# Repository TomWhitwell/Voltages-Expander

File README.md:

# Voltages Expander for the Turing Machine 

Hardware documentation for the old Voltages Fader Expander for the Music Thing Modular Turing Machine, published CC-BY-SA. 

For more details, visit http://www.musicthing.co.uk/

Qty | Value | Device | Parts | Description | Mouser
-- | -- | -- | -- | -- | --
8 | 50k | Illuminated Fader | GATE1, GATE2, GATE3, GATE4, GATE5, GATE6, GATE7, GATE8 | 20mm Alpha Illuminated Fader | 312-2045F-R50K
1 | 10k | 9mm pot | SCALE | 9 mm vertical pot, D shaft | 688-RK09K1130AH1
1 | 50k | 9mm pot | OFFSET | 9 mm vertical pot, D shaft | 652-PTV09A-4025FB503
2 | 100n | C-EU025-024X044 | C1, C2 | CAPACITOR | 594-K104K15X7RF5TH5
1 | TL074 | TL074 | IC1 | OP AMP | 595-TL074CN
1 |   | MA08-2 | GATES | PIN HEADER 2x8 | 649-67997-216HLF
1 | 78L09 |   | 78L1 | Positive VOLTAGE REGULATOR | 511-L78L09ACZ
6 | 10k | R-EU_0207/10 | R3, R4, R5, R6, R7, R8 | RESISTOR | 660-MF1/4DCT52A1002F
4 | 1k | R-EU_0207/10 | R1, R2, R9, R10 | RESISTOR | 660-MF1/4DCT52R1001F
1 | 10k | RN08 | RN1 | Resistor Network 9 pin, 8 resistors, bussed | 652-4609X-1LF-10K
1 | 2k | RN08 | RN2 | Resistor Network 9 pin, 8 resistors, bussed | 652-4609X-1LF-2K
3 | PJ-301B | PJ-301B | CLOCK_OUT, INVERT_OUT, MAIN_OUT | Sockets | Available from Erthenvar or Thonk
1 |   |   | 14 pin DIP socket |   | 649-DILB14P-223TLF
  |   |   |   |   |

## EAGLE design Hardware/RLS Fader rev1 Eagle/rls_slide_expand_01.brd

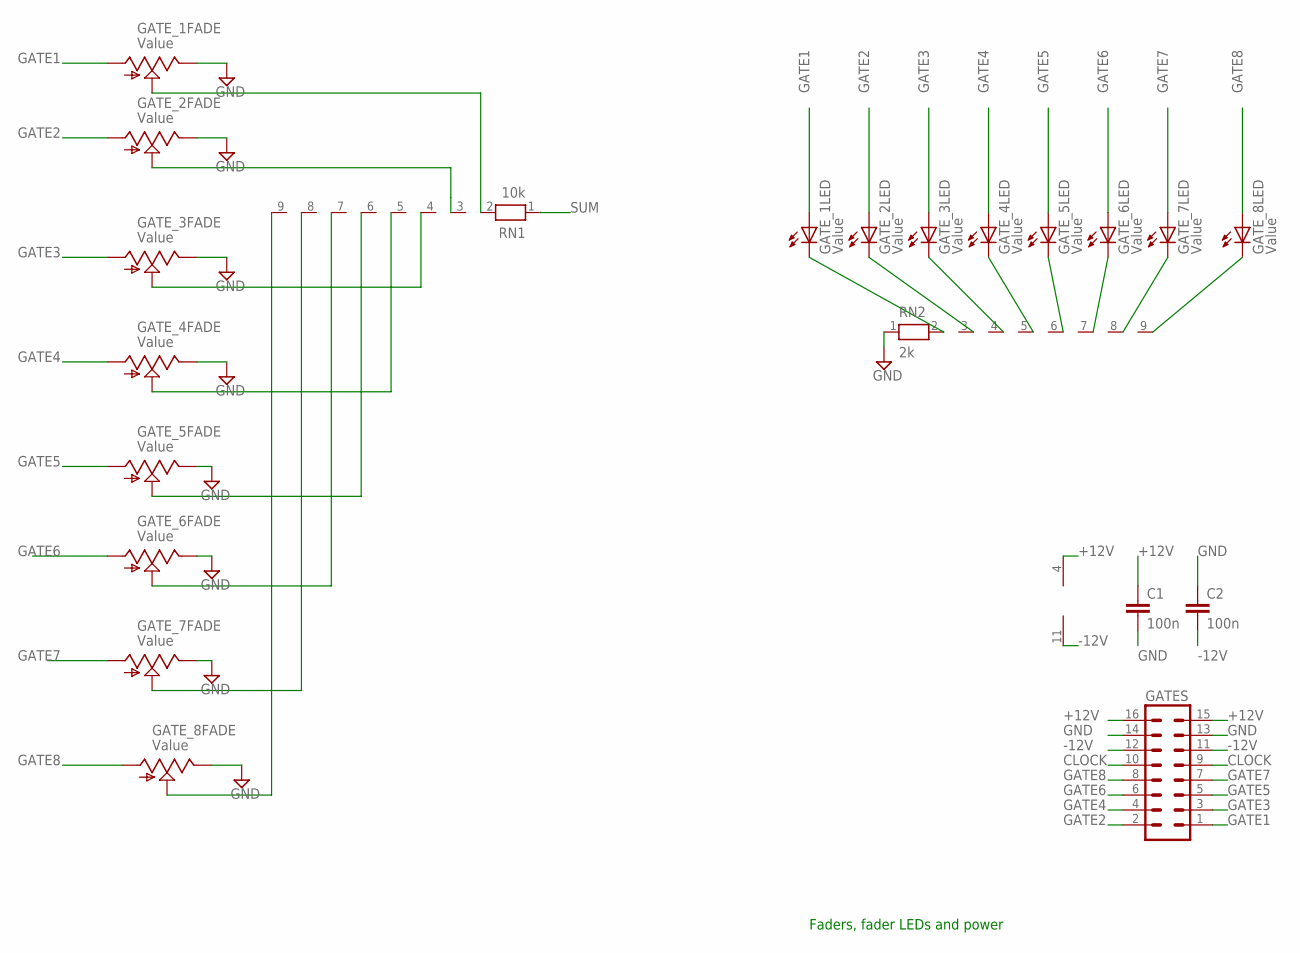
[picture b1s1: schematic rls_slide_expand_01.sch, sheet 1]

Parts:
C1, C2: 100n; C050-024X044
GATES: MA08-2
GATE_1, GATE_2, GATE_3, GATE_4, GATE_5, GATE_6, GATE_7, GATE_8: Value; ALPHA_ILL_FADER_20MM
IC1: TL074P; DIL14
RN1: 10k; RN-9
RN2: 2k; RN-9

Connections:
+12V: C1.1, GATES.15, GATES.16, IC1.4 (V+); also elsewhere on the board
-12V: C2.2, GATES.11, GATES.12, IC1.11 (V-)
CLOCK: GATES.9, GATES.10; also elsewhere on the board
GATE1: GATES.1, GATE_1.3 (A), GATE_1.B (A)
GATE2: GATES.2, GATE_2.3 (A), GATE_2.B (A)
GATE3: GATES.3, GATE_3.3 (A), GATE_3.B (A)
GATE4: GATES.4, GATE_4.3 (A), GATE_4.B (A)
GATE5: GATES.5, GATE_5.3 (A), GATE_5.B (A)
GATE6: GATES.6, GATE_6.3 (A), GATE_6.B (A)
GATE7: GATES.7, GATE_7.3 (A), GATE_7.B (A)
GATE8: GATES.8, GATE_8.3 (A), GATE_8.B (A)
GND: C1.2, C2.1, GATES.13, GATES.14, GATE_1.1 (E), GATE_2.1 (E), GATE_3.1 (E), GATE_4.1 (E), GATE_5.1 (E), GATE_6.1 (E), GATE_7.1 (E), GATE_8.1 (E), RN2.1; also elsewhere on the board
unnamed: GATE_1.2 (S), RN1.2
unnamed: GATE_1.E (C), RN2.2
unnamed: GATE_2.2 (S), RN1.3
unnamed: GATE_2.E (C), RN2.3
unnamed: GATE_3.E (C), RN2.4
unnamed: GATE_3.2 (S), RN1.4
unnamed: GATE_4.2 (S), RN1.5
unnamed: GATE_5.2 (S), RN1.6
unnamed: GATE_6.2 (S), RN1.7
unnamed: GATE_7.2 (S), RN1.8
unnamed: GATE_8.2 (S), RN1.9
unnamed: GATE_4.E (C), RN2.5
unnamed: GATE_6.E (C), RN2.7
unnamed: GATE_5.E (C), RN2.6
unnamed: GATE_7.E (C), RN2.8
unnamed: GATE_8.E (C), RN2.9
SUM: RN1.1; also elsewhere on the board

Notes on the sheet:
Faders, fader LEDs and power

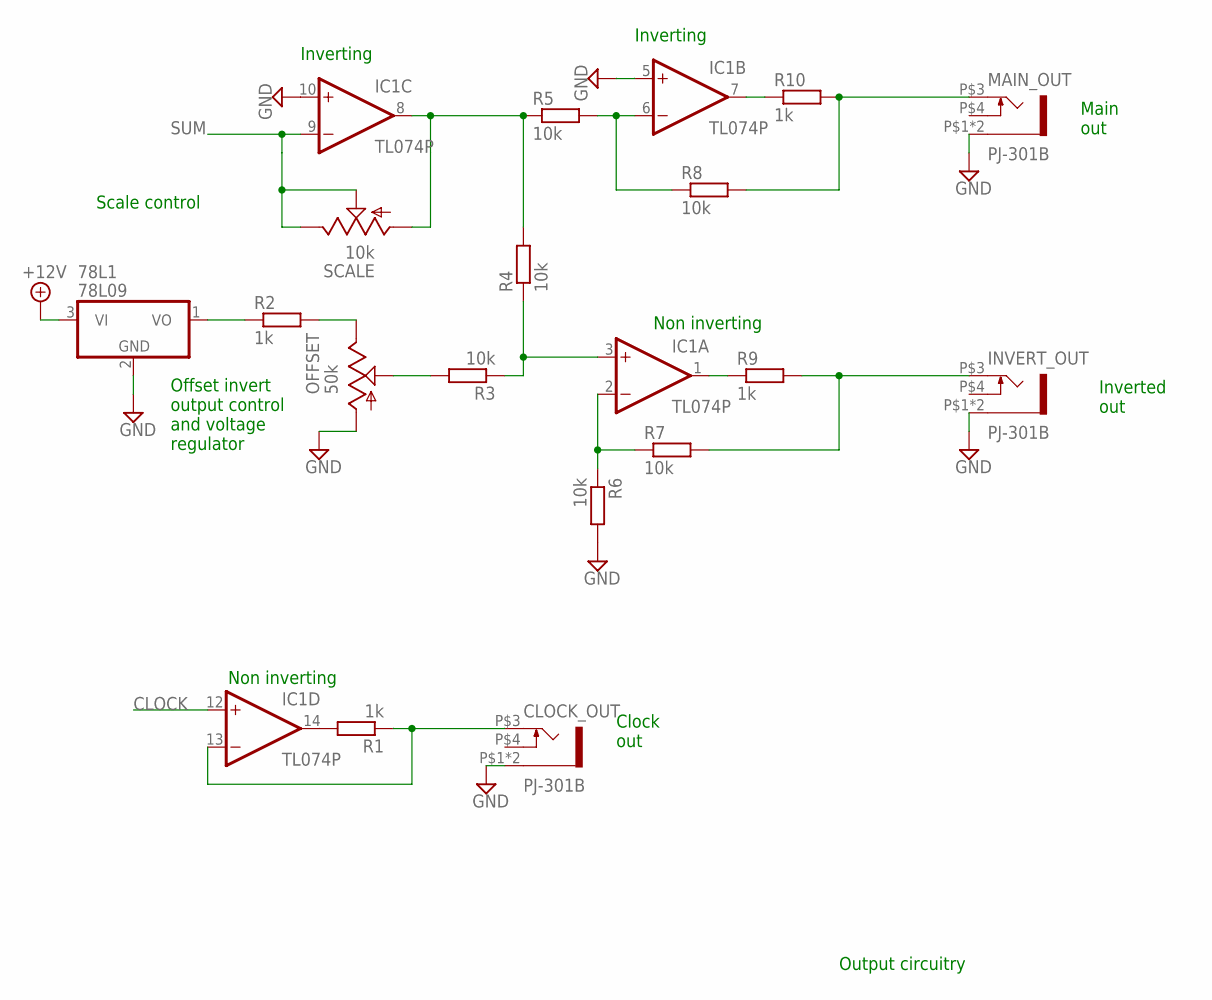
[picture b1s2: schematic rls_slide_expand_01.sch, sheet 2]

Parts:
78L1: 78L09; TO92
CLOCK_OUT: PJ-301B
IC1: TL074P; DIL14
INVERT_OUT: PJ-301B
MAIN_OUT: PJ-301B
OFFSET: 50k; EVUF
R1, R2, R9, R10: 1k; 0207/10
R3, R4, R5, R6, R7, R8: 10k; 0207/10
SCALE: 10k; EVUF

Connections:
+12V: 78L1.3 (VI); also elsewhere on the board
CLOCK: IC1.12 (+IN); also elsewhere on the board
GND: 78L1.2 (GND), CLOCK_OUT.P$1 (5), CLOCK_OUT.P$2 (5), IC1.5 (+IN), IC1.10 (+IN), INVERT_OUT.P$1 (5), INVERT_OUT.P$2 (5), MAIN_OUT.P$1 (5), MAIN_OUT.P$2 (5), OFFSET.1 (A), R6.2; also elsewhere on the board
unnamed: IC1.6 (-IN), R5.2, R8.1
unnamed: MAIN_OUT.P$3 (3), R8.2, R10.2
unnamed: IC1.7 (OUT), R10.1
unnamed: OFFSET.3 (E), R2.2
unnamed: IC1.1 (OUT), R9.1
unnamed: OFFSET.2 (S), R3.2
unnamed: IC1.3 (+IN), R3.1, R4.1
unnamed: IC1.2 (-IN), R6.1, R7.1
unnamed: INVERT_OUT.P$3 (3), R7.2, R9.2
unnamed: IC1.8 (OUT), R4.2, R5.1, SCALE.1 (A)
unnamed: IC1.14 (OUT), R1.2
unnamed: CLOCK_OUT.P$3 (3), IC1.13 (-IN), R1.1
unnamed: 78L1.1 (VO), R2.1
SUM: IC1.9 (-IN), SCALE.2 (S), SCALE.3 (E); also elsewhere on the board

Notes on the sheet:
Scale control
Offset invert output control and voltage regulator
Main out
Inverted out
Clock out
Output circuitry
Inverting
Non inverting

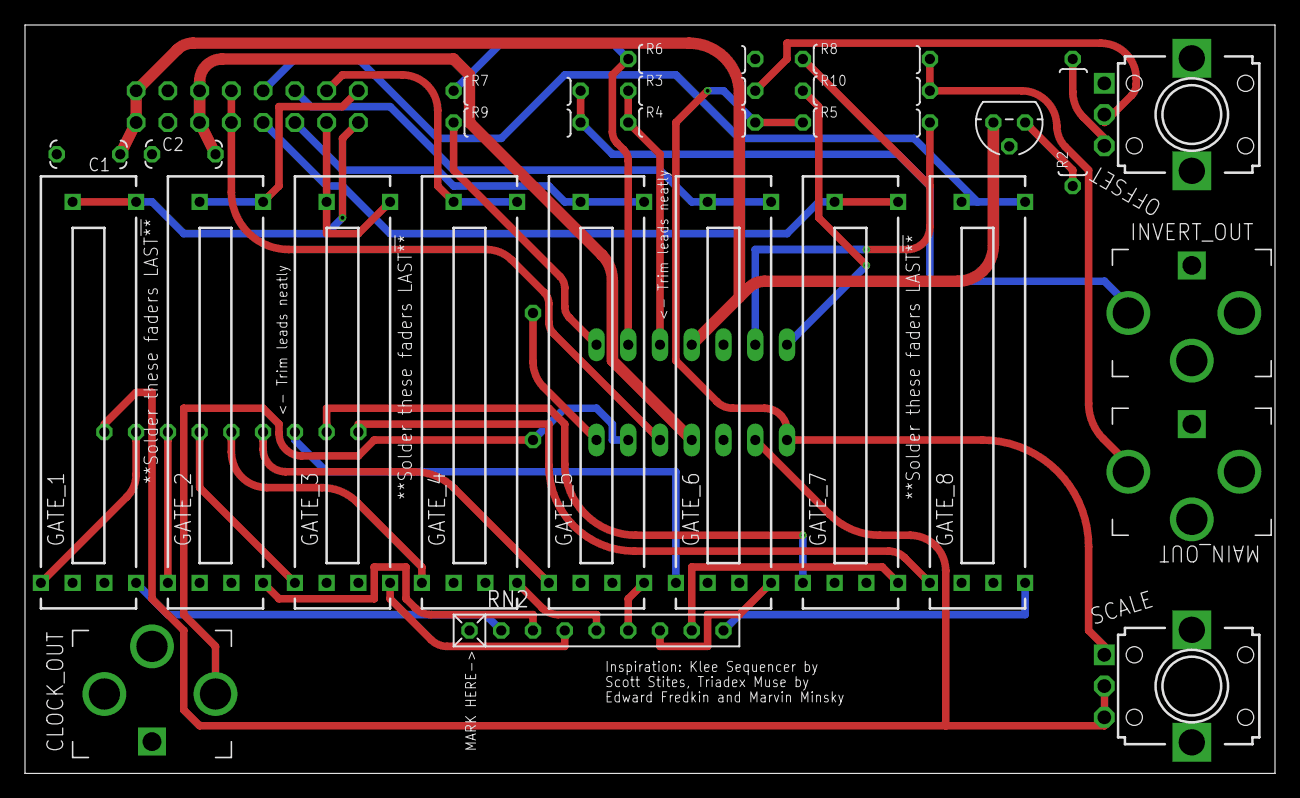
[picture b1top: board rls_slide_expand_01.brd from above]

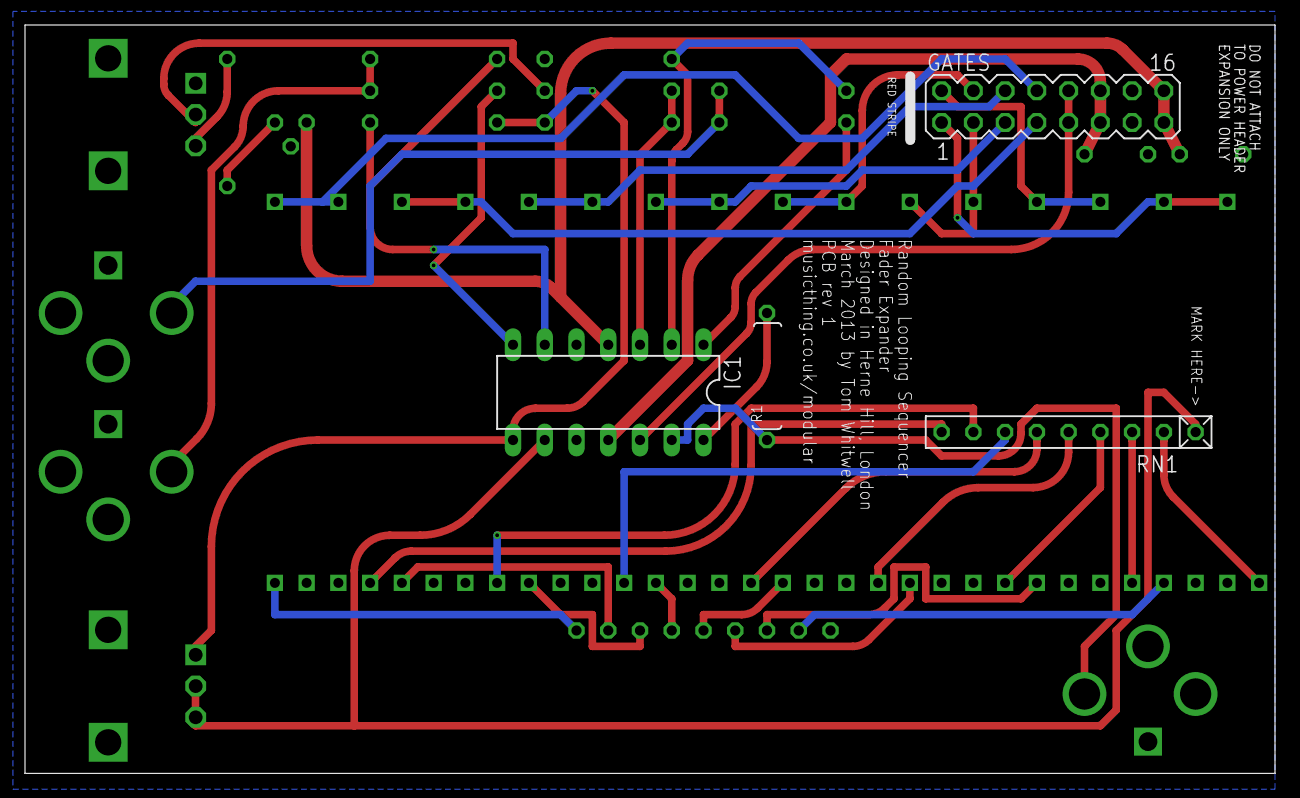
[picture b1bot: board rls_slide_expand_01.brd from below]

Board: 2 copper layers, 100.0 x 59.9 mm, 30 parts (4 on the bottom side), 42 nets.

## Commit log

2018-01-03 Upload files
